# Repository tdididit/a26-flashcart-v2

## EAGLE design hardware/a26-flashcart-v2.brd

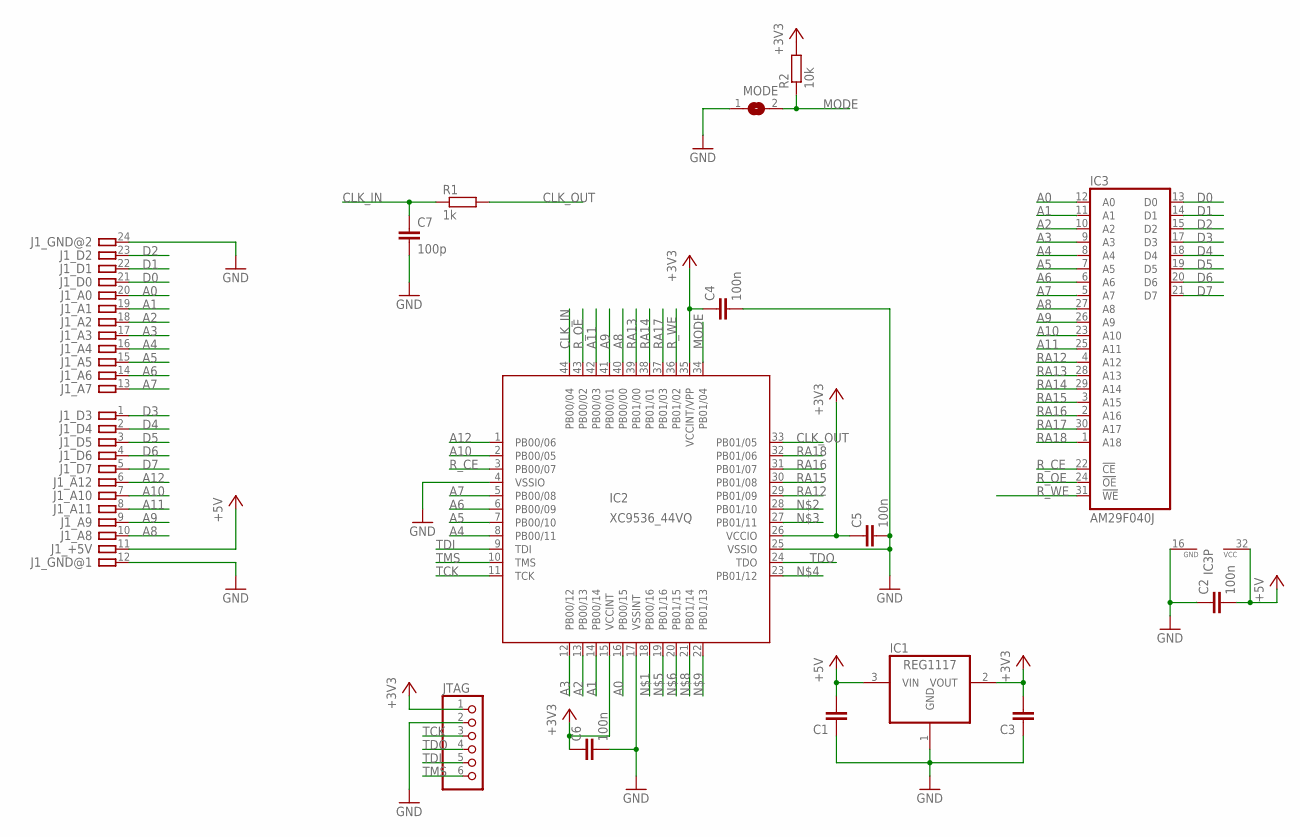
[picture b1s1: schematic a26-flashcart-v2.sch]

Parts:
C1, C3: C-EUC0805; C0805
C2, C4, C5, C6: 100n; C0805
C7: 100p; C0805
IC1: REG1117; SOT223
IC2: XC9536_44VQ; SQFP-S-10X10-44
IC3: AM29F040J; PLCC32R
J1: ATARI-2600-SMALL
JTAG: PINHD-1X6; 1X06
MODE: SJ
R1: 1k; R0805
R2: 10k; R0805

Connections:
+3V3: C3.2, C4.1, C5.1, C6.1, IC1.2 (VOUT), IC2.15 (VCCINT), IC2.26 (VCCIO), IC2.35 (VCCINT/VPP), JTAG.1, R2.2
+5V: C1.2, C2.2, IC1.3 (VIN), IC3.32 (VCC), J1.11
A0: IC2.16 (PB00/15), IC3.12 (A0), J1.20
A1: IC2.14 (PB00/14), IC3.11 (A1), J1.19
A2: IC2.13 (PB00/13), IC3.10 (A2), J1.18
A3: IC2.12 (PB00/12), IC3.9 (A3), J1.17
A4: IC2.8 (PB00/11), IC3.8 (A4), J1.16
A5: IC2.7 (PB00/10), IC3.7 (A5), J1.15
A6: IC2.6 (PB00/09), IC3.6 (A6), J1.14
A7: IC2.5 (PB00/08), IC3.5 (A7), J1.13
A8: IC2.40 (PB00/00), IC3.27 (A8), J1.10
A9: IC2.41 (PB00/01), IC3.26 (A9), J1.9
A10: IC2.2 (PB00/05), IC3.23 (A10), J1.7
A11: IC2.42 (PB00/03), IC3.25 (A11), J1.8
A12: IC2.1 (PB00/06), J1.6
CLK_IN: C7.1, IC2.44 (PB00/04), R1.1
CLK_OUT: IC2.33 (PB01/05), R1.2
D0: IC3.13 (D0), J1.21
D1: IC3.14 (D1), J1.22
D2: IC3.15 (D2), J1.23
D3: IC3.17 (D3), J1.1
D4: IC3.18 (D4), J1.2
D5: IC3.19 (D5), J1.3
D6: IC3.20 (D6), J1.4
D7: IC3.21 (D7), J1.5
GND: C1.1, C2.1, C3.1, C4.2, C5.2, C6.2, C7.2, IC1.1 (GND), IC2.4 (VSSIO), IC2.17 (VSSINT), IC2.25 (VSSIO), IC3.16 (GND), J1.12, J1.24, JTAG.2, MODE.1
MODE: IC2.34 (PB01/04), MODE.2, R2.1
RA12: IC2.29 (PB01/09), IC3.4 (A12)
RA13: IC2.39 (PB01/00), IC3.28 (A13)
RA14: IC2.38 (PB01/01), IC3.29 (A14)
RA15: IC2.30 (PB01/08), IC3.3 (A15)
RA16: IC2.31 (PB01/07), IC3.2 (A16)
RA17: IC2.37 (PB01/03), IC3.30 (A17)
RA18: IC2.32 (PB01/06), IC3.1 (A18)
R_CE: IC2.3 (PB00/07), IC3.22 (!CE)
R_OE: IC2.43 (PB00/02), IC3.24 (!OE)
R_WE: IC2.36 (PB01/02), IC3.31 (!WE)
TCK: IC2.11 (TCK), JTAG.3
TDI: IC2.9 (TDI), JTAG.5
TDO: IC2.24 (TDO), JTAG.4
TMS: IC2.10 (TMS), JTAG.6

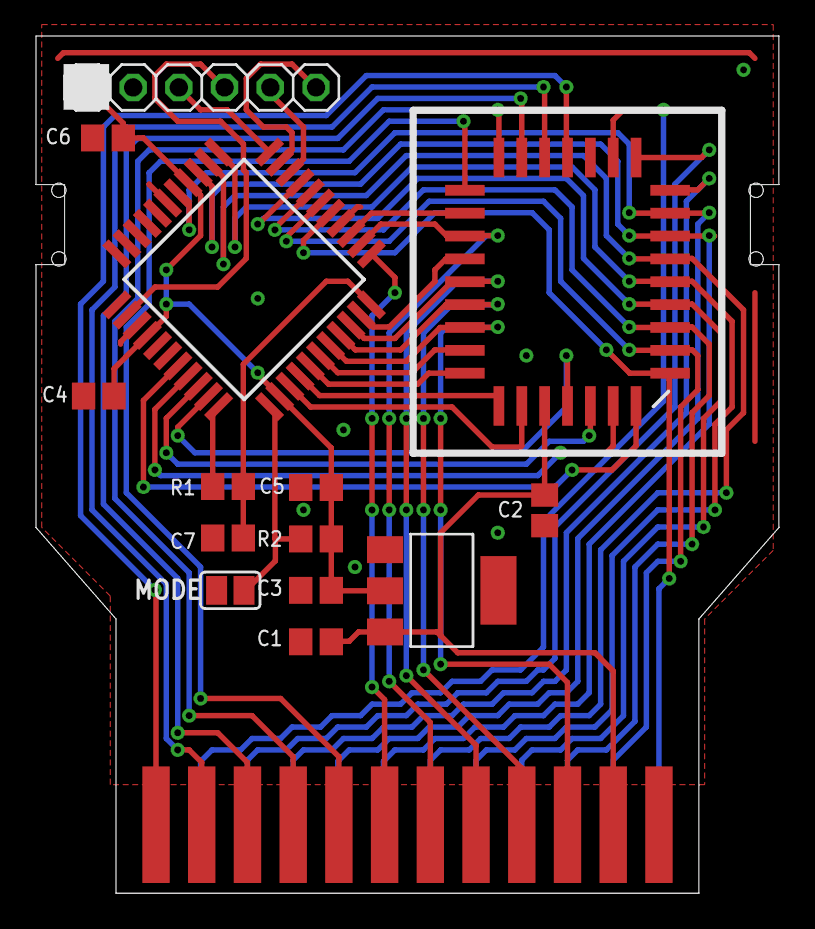
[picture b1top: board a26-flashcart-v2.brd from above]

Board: 2 copper layers, 41.3 x 47.6 mm, 15 parts (0 on the bottom side), 41 nets.

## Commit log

2018-10-05 initial repository
2018-10-05 updated zip
